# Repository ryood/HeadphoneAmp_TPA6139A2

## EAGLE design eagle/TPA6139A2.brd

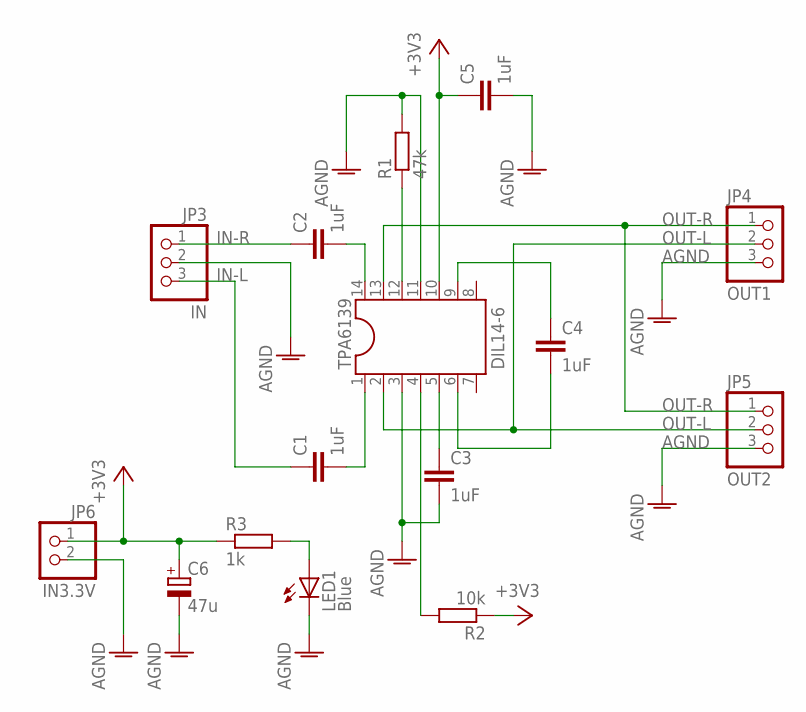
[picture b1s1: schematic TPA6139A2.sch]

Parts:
C1, C2: 1uF; C050-050X075
C3, C4, C5: 1uF; C050-024X044
C6: 47u; TT2D5L
JP3: IN; 1X03
JP4: OUT1; 1X03
JP5: OUT2; 1X03
JP6: IN3.3V; 1X02
LED1: Blue; LED3MM
R1: 47k; 0207/7
R2: 10k; 0207/7
R3: 1k; 0207/7
TPA6139: DIL14-6

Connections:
+3V3: C5.1, C6.+, JP6.1, R2.1, R3.1, TPA6139.10
AGND: C3.2, C5.2, C6.-, JP3.2, JP4.3, JP5.3, JP6.2, LED1.K (C), R1.2, TPA6139.3, TPA6139.11
IN-L: C1.1, JP3.3
IN-R: C2.1, JP3.1
unnamed: C2.2, TPA6139.14
unnamed: C1.2, TPA6139.1
unnamed: R2.2, TPA6139.4
unnamed: C3.1, TPA6139.5
unnamed: R1.1, TPA6139.12
unnamed: LED1.A, R3.2
unnamed: C4.2, TPA6139.6
unnamed: C4.1, TPA6139.9
OUT-L: JP4.2, JP5.2, TPA6139.2
OUT-R: JP4.1, JP5.1, TPA6139.13

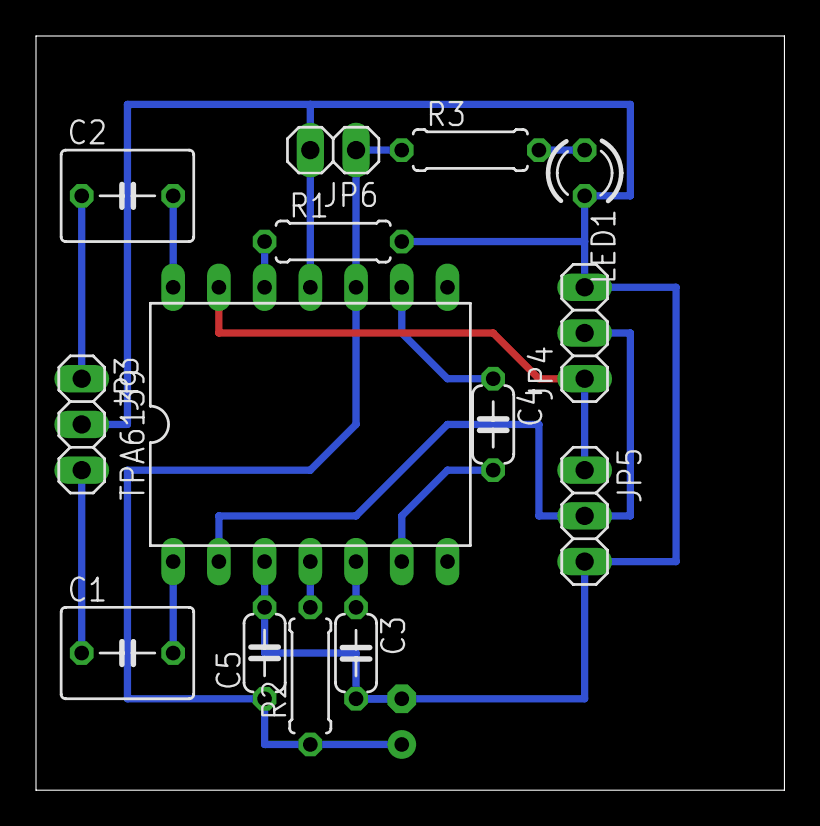
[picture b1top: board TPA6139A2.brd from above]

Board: 2 copper layers, 41.6 x 41.9 mm, 15 parts (1 on the bottom side), 14 nets.

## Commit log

2015-07-18 テスト表追加
2015-07-18 回路図、基板図修正
2015-07-18 ケース内配線図追加
2015-07-18 ケース加工図追加
